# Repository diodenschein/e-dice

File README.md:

# e-dice
electronic dice kit for learning basic soldering. 

An attiny13 , a button, resistors and some LEDs ;-)

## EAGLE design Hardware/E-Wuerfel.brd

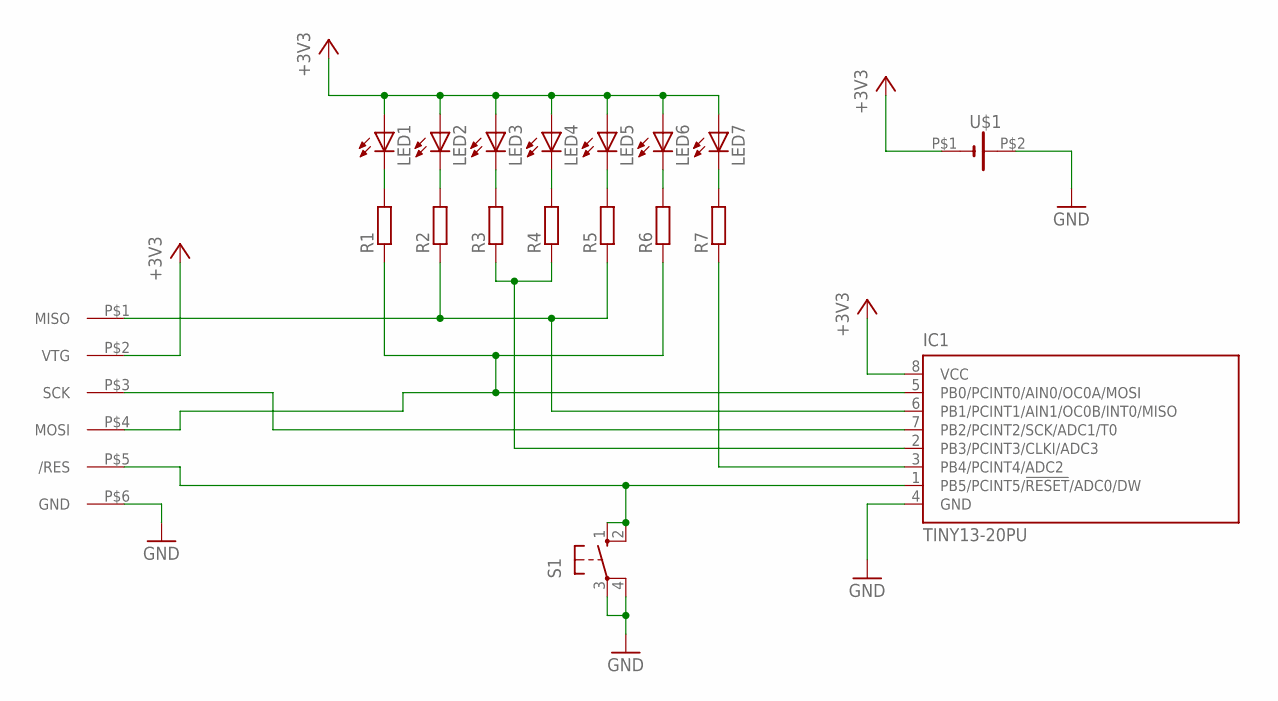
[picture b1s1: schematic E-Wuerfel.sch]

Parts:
IC1: TINY13-20PU; DIL08
LED1, LED2, LED3, LED4, LED5, LED6, LED7: LED5MM
R1, R2, R3, R4, R5, R6, R7: R-EU_0207/7; 0207/7
S1: 10-XX; B3F-10XX
U$1: 2XAA; 2AAMOUNT
U$2: AVRISP1.27; 2X6-127

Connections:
+3V3: IC1.8 (VCC), LED1.A, LED2.A, LED3.A, LED4.A, LED5.A, LED6.A, LED7.A, U$1.P$1 (-), U$2.P$2 (VTG)
GND: IC1.4 (GND), S1.3, S1.4 (P1), U$1.P$2 (+), U$2.P$6 (GND)
unnamed: LED1.K (C), R1.2
unnamed: LED2.K (C), R2.2
unnamed: LED3.K (C), R3.2
unnamed: LED4.K (C), R4.2
unnamed: LED5.K (C), R5.2
unnamed: LED6.K (C), R6.2
unnamed: IC1.5 (PB0/PCINT0/AIN0/OC0A/MOSI), R1.1, R6.1, U$2.P$4 (MOSI)
unnamed: IC1.1 (PB5/PCINT5/!RESET!/ADC0/DW), S1.1 (S), S1.2 (S1), U$2.P$5 (/RES)
unnamed: IC1.2 (PB3/PCINT3/CLKI/ADC3), R3.1, R4.1
unnamed: IC1.6 (PB1/PCINT1/AIN1/OC0B/INT0/MISO), R2.1, R5.1, U$2.P$1 (MISO)
unnamed: LED7.K (C), R7.2
unnamed: IC1.3 (PB4/PCINT4/ADC2), R7.1
unnamed: IC1.7 (PB2/PCINT2/SCK/ADC1/T0), U$2.P$3 (SCK)

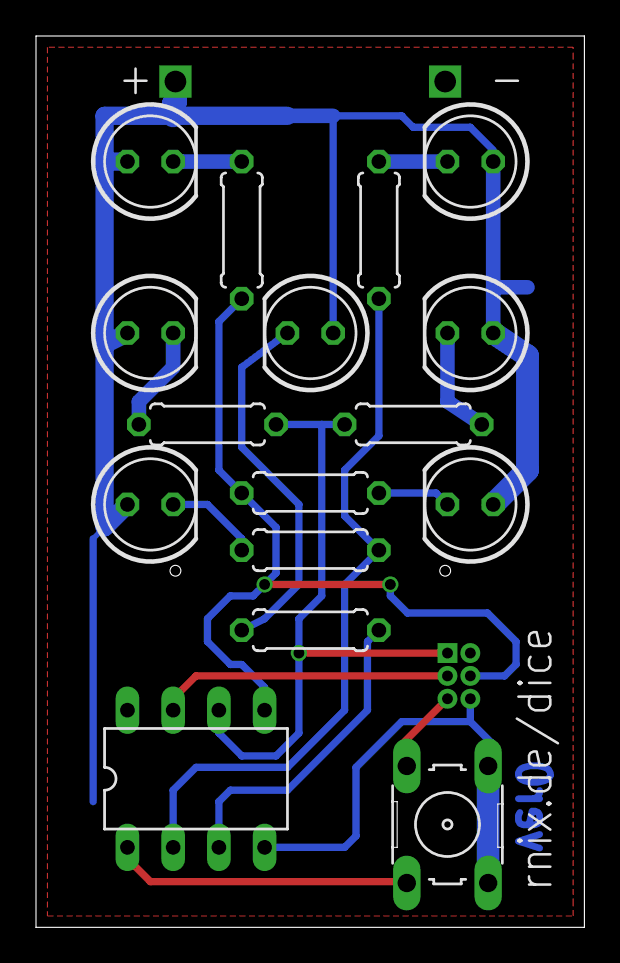
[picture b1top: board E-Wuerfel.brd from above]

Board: 2 copper layers, 30.5 x 49.5 mm, 18 parts (0 on the bottom side), 15 nets.

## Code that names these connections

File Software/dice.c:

#include <avr/io.h>
 #include <avr/sleep.h>
 #include <avr/interrupt.h>
#include <util/delay.h>
#include <stdlib.h>


#ifndef F_CPU
#define F_CPU 128000UL
#endif

#define CENTER PB4
#define TLBR PB0
#define LR PB1
#define BLTR PB3

volatile uint8_t stop=0;


void show(uint8_t number){ //numBer to Dice 

	switch(number){
		case 1:
			PORTB &= ~(1 << CENTER);
			break;
		case 2:
			PORTB &= ~(1 << TLBR);
			break;
		case 3:
			PORTB &= ~((1 << BLTR)|(1 << CENTER));
			break;
		case 4:
			PORTB &= ~((1 << TLBR)|(1 << BLTR));
			break;
		case 5:
			PORTB &= ~((1 << TLBR)|(1 << BLTR)|(1 << CENTER));
			break;
		case 6:
			PORTB &= ~((1 << TLBR)|(1 << BLTR)|(1 << LR));
			break;
		default: 
			PORTB &= ~((1 << TLBR)|(1 << BLTR)|(1 << CENTER)|(1 << LR));
			break;
	}
}

void clear(){//clear dice
	PORTB |= ((1 << PB0)|(1 << PB1)|(1 << PB3)|(1 << PB4));
	}


void setup(){

  // Configure LED pins as output, turn LEDS off
  DDRB |= ((1 << CENTER)|(1 << TLBR)|(1 << BLTR)|(1 << LR));
  PORTB |= ((1 << CENTER)|(1 << TLBR)|(1 << BLTR)|(1 << LR));
  //configure Button pin as input with Pullup
  DDRB &= ~(1 << PB5);
  PORTB |= (1 << PB5);
	sleep_enable();
	PCMSK |= (1 << PCINT5); //Pin change interrupt mask for PB5 enabled
	GIMSK |= (1 << PCIE); //Pin change interrupt enable
}


void cast(void){
	TIMSK0= 0x00;
  	TCCR0B = 0x00;  //Timer-Stop
	TCNT0=0x00;
	while(!( PINB & ( 1<<PB5 ) )){
        uint8_t a=1;//rand()%6+1;
	clear();
	show(a);
	}

	stop=0;
	TCCR0B|=((1<<CS02)|(1<<CS00));  //Prescaler=1024, Timer-Start
	TIMSK0|=(1<<TOIE0);        //IRQ-Enable;
}





int main(void) {
	
	setup();
	sei();

    TCCR0B|=((1<<CS02)|(1<<CS00));  //Prescaler=1024, Timer-Start
	TIMSK0|=(1<<TOIE0);        //IRQ-Enable;
	show(7);
while(1){
	if(stop){
		clear();
		set_sleep_mode(SLEEP_MODE_PWR_DOWN);
  		sleep_mode();
		}		
	}
}

ISR(TIM0_OVF_vect){

	TIMSK0= 0x00;
  	TCCR0B = 0x00;  //Timer-Stop
	stop=1;
}

ISR(PCINT0_vect){
	cli();
	cast();
	sei();
}

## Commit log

2015-06-06 init
2015-06-06 added image
2015-06-06 image fix
2015-06-06 image resize
2015-06-06 Revert "image resize"
    This reverts commit b1151b008634067300a4287c166478a138d59ddb.
2015-06-06 added schematic pdf
2015-06-10 added gitignore
2015-06-10 added default/wq to gitignore
2015-09-18 added german manual
